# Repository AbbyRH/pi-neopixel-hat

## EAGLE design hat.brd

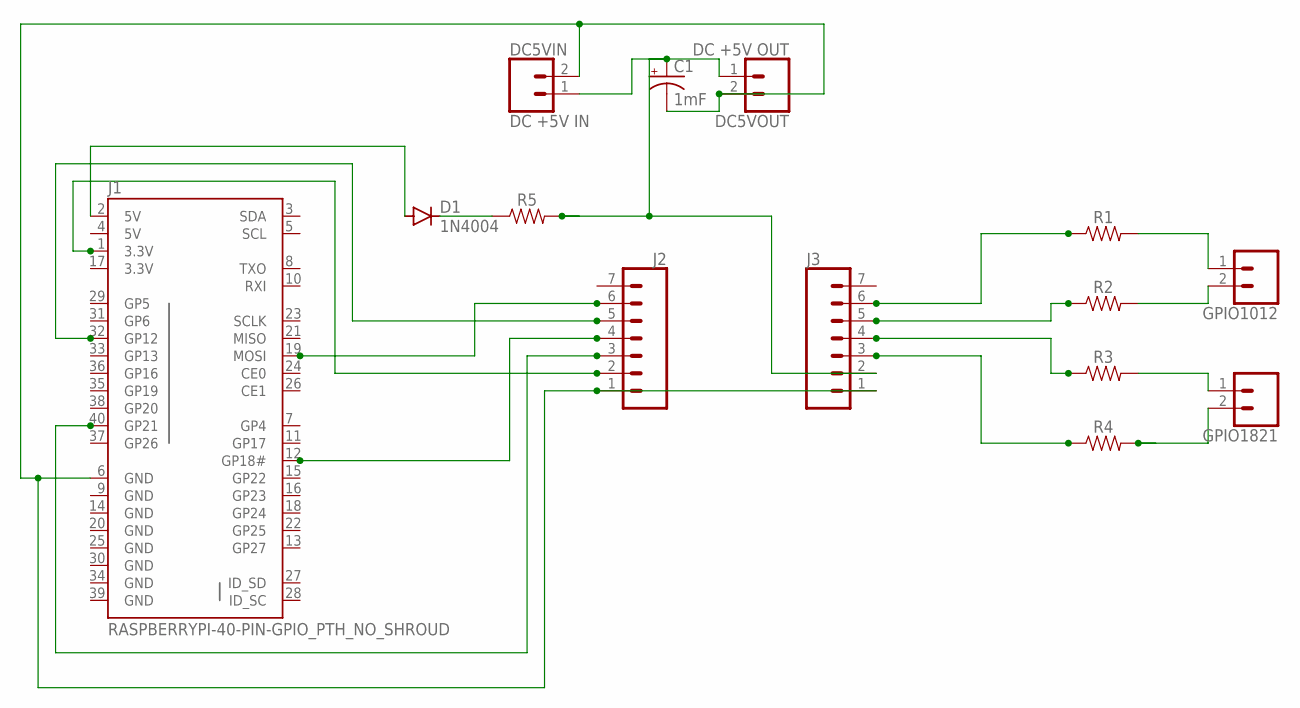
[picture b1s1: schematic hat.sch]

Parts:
C1: 1mF; CPOL-RADIAL-5MM-10MM
D1: 1N4004; DO41-10
DC5VIN: DC +5V IN; 1X02_XTRA_BIG
DC5VOUT: DC +5V OUT; 1X02_XTRA_BIG
GPIO1012, GPIO1821: CONN_02PTH4; 1X02_XTRA_BIG
J1: RASPBERRYPI-40-PIN-GPIO_PTH_NO_SHROUD; 2X20
J2, J3: CONN_07; 1X07
R1, R2, R3, R4, R5: AXIAL-0.3

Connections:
3.3V: J1.1 (3.3V), J1.17 (3.3V), J2.2
3.3VGP10: J1.19 (MOSI), J2.6
3.3VGP12: J1.32 (GP12), J2.5
3.3VGP18: J1.12 (GP18#), J2.4
3.3VGP21: J1.40 (GP21), J2.3
5V: D1.A, J1.2 (5V), J1.4 (5V)
5VGP10: J3.6, R1.P$1 (1)
5VGP12: J3.5, R2.P$1 (1)
5VGP18: J3.4, R3.P$1 (1)
5VGP21: J3.3, R4.P$1 (1)
GND: C1.-, DC5VIN.2, DC5VOUT.2, J1.6 (GND), J1.9 (GND), J1.14 (GND), J1.20 (GND), J1.25 (GND), J1.30 (GND), J1.34 (GND), J1.39 (GND), J2.1, J3.1
GP10: GPIO1012.1, R1.P$2 (2)
GP12: GPIO1012.2, R2.P$2 (2)
GP18: GPIO1821.1, R3.P$2 (2)
GP21: GPIO1821.2, R4.P$2 (2)
unnamed: D1.C, R5.P$1 (1)
unnamed: C1.+, DC5VIN.1, DC5VOUT.1, J3.2, R5.P$2 (2)

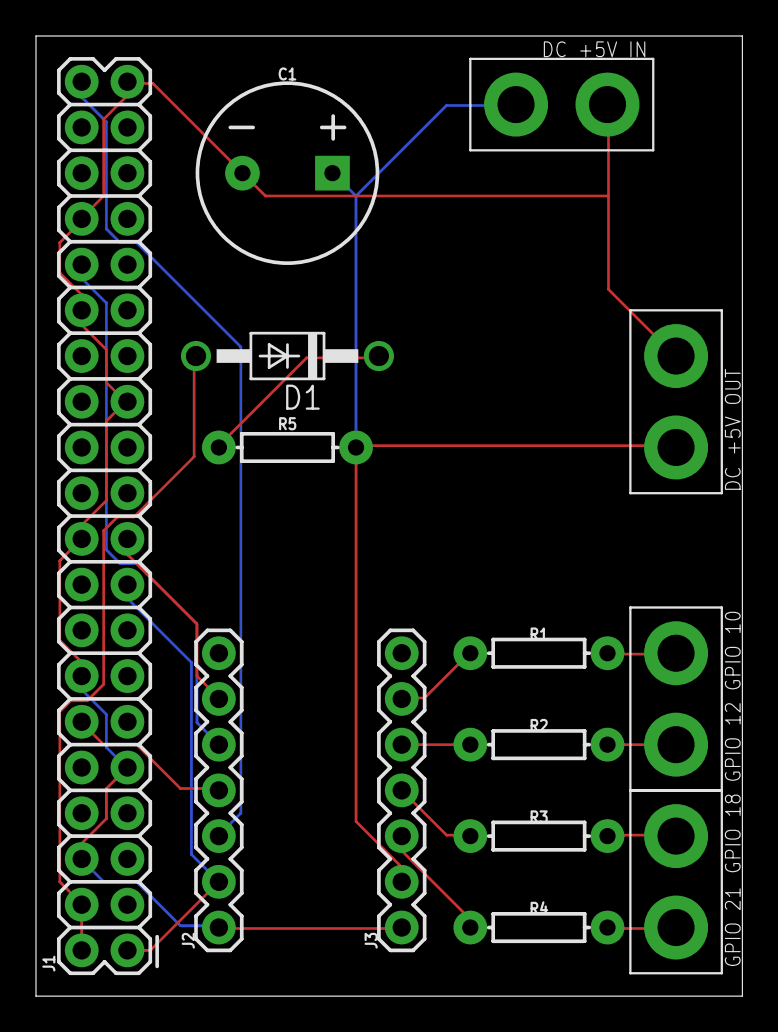
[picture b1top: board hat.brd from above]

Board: 2 copper layers, 39.2 x 53.3 mm, 14 parts (0 on the bottom side), 17 nets.

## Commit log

2019-06-12 wip hat
2019-06-13 hat layout
2019-06-13 tweaks
2019-06-13 shrunk board, double sided

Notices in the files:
parts and their libraries:
SparkFun-Connectors: Licensing: Creative Commons ShareAlike 4.0 International - https://creativecommons.org/licenses/by-sa/4.0
